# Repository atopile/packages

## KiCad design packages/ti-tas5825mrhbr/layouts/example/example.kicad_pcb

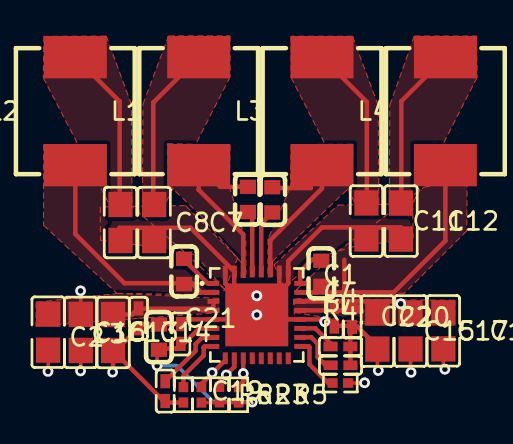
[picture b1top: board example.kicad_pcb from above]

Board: 2 copper layers, 32 parts (0 on the bottom side), 23 nets.

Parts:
C1, C4, C19: 1µF ±10% 25V X5R; C0402
C2: 4.7µF ±10% 16V X5R; C0603
C3: 100nF ±10% 16V X7R; C0402
C5, C6, C9, C10: 470nF ±10% 50V X7R; C0603
C7, C8, C11, C12: 680nF ±10% 50V X7R; C0805
C13, C14, C15, C16, C17, C18: 10µF ±10% 50V X5R; C0805
C20, C21, C22: 100nF ±10% 50V X7R; C0402
L1, L2, L3, L4: IND-SMD_L7.3-W6.8
R2, R3, R4, R5: 10kΩ ±1% 62.5mW; R0402
R6: 4.7kΩ ±1% 62.5mW; R0402
U1: VQFN-32_L5.0-W5.0-P0.50-TL-EP

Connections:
ADR: R6.1, U1.8
AVDD: C1.1, U1.19
BST_Aneg: C5.1, U1.29
BST_Apos: C6.1, U1.1
BST_Bneg: C9.1, U1.28
BST_Bpos: C10.1, U1.24
GPIO0: R2.1, U1.9
GPIO1: R3.1, U1.10
GPIO2: R5.1, U1.11
GVDD: C4.1, U1.18
OUT_Aneg: C5.2, L1.1, U1.30
OUT_Apos: C6.2, L2.1, U1.2
OUT_Bneg: C9.2, L3.1, U1.27
OUT_Bpos: C10.2, L4.1, U1.23
PVDD: C13.1, C14.1, C15.1, C16.1, C17.1, C18.1, C20.1, C21.1, C22.1, U1.3, U1.4, U1.21, U1.22
VR_DIG: C19.1, U1.7
amp-line-0: C7.1, L1.2
amp-line-1: C8.1, L2.2
amp-line-2: C11.1, L3.2
amp-line-3: C12.1, L4.2
gnd: C1.2, C2.2, C3.2, C4.2, C7.2, C8.2, C11.2, C12.2, C13.2, C14.2, C15.2, C16.2, C17.2, C18.2, C19.2, C20.2, C21.2, C22.2, R6.2, U1.5, U1.20, U1.25, U1.26, U1.31, U1.32, U1.33
hv: C2.1, C3.1, R2.2, R3.2, R4.2, R5.2, U1.6
nPDN: R4.1, U1.17

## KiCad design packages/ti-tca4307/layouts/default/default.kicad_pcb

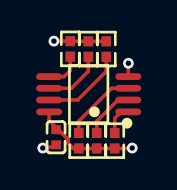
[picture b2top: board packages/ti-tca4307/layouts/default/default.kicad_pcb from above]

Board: 2 copper layers, 8 parts (0 on the bottom side), 8 nets.

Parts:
C1: 0F; C0402
R1, R2, R3, R4, R5, R6: 10000Ω; R0402
U1: VSSOP-8_L3.0-W3.0-P0.65-LS4.9-BL

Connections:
EN: R1.2, U1.1
READY: R6.2, U1.5
SCL: R2.1, U1.2
SDA: R3.1, U1.7
hv: C1.1, R1.1, R2.2, R3.2, R4.2, R5.2, R6.1, U1.8
i2c_upstream-SCL: R4.1, U1.3
i2c_upstream-SDA: R5.1, U1.6
lv: C1.2, U1.4

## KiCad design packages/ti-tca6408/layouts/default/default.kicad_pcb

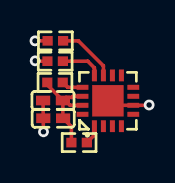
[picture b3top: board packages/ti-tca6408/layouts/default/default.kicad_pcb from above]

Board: 2 copper layers, 7 parts (0 on the bottom side), 6 nets.

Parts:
C1, C2: 1±5.0%F; C0402
R1, R2, R3, R4: 4700±1.0%Ω; R0402
U1: QFN-16_L3.0-W3.0-P0.50-BL-EP1.7

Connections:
SCL: R2.1, U1.12
SDA: R3.1, U1.13
hv: C1.1, C2.1, R1.1, R2.2, R3.2, R4.1, U1.14, U1.15
lv: C1.2, C2.2, U1.6, U1.16, U1.17
nINT: R4.2, U1.11
nRESET: R1.2, U1.1

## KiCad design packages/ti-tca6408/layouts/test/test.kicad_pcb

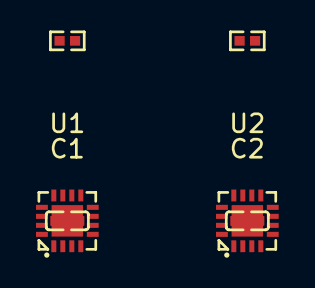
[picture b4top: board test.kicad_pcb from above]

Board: 2 copper layers, 6 parts (0 on the bottom side), 6 nets.

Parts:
C1, C2: 100nF ±10% 16V X7R; C0402
R1, R2: 10kΩ ±1% 62.5mW; R0402
U1, U2: QFN-16_L3.0-W3.0-P0.50-BL-EP1.7

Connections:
SCL: U1.12, U2.12
SDA: U1.13, U2.13
VCCI: C1.1, C2.1, R1.2, R2.2, U1.14, U1.15, U2.14, U2.15, U2.16
expanders[0]-RESET: R1.1, U1.1
expanders[1]-RESET: R2.1, U2.1
gnd: C1.2, C2.2, U1.6, U1.16, U1.17, U2.6, U2.17

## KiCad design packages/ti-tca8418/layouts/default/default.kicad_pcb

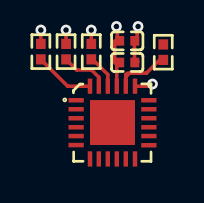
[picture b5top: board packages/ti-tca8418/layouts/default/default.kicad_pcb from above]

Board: 2 copper layers, 7 parts (0 on the bottom side), 6 nets.

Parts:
C1: 1±10.0%F; C0402
C2: {7.999..1.2}F; C0402
R1, R2, R3, R4: 10000±1.0%Ω; R0402
U1: WQFN-24_L4.0-W4.0-P0.50-TL-EP2.5

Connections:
SCL: R1.1, U1.23
SDA: R2.1, U1.22
hv: C1.1, C2.1, R1.2, R2.2, R4.2, U1.21
lv: C1.2, C2.2, R3.2, U1.19
nINT: R3.1, U1.24
nRESET: R4.1, U1.20
